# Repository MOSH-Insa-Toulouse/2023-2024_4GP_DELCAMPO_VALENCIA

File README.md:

# **Projet Capteur**

## Introduction 

## Sommaire

***
  - [Livrables](#livrables)
  - [PCB Shield](#pcb-shield)
  - [Code Arduino de Mesure](#code-arduino-de-mesure)
  - [APK pour Android](#apk-pour-android)
  - [Banc de test](#banc-de-test)
  - [Code Arduino de Mesure](#code-arduino-de-mesure)
  - [Datasheet du capteur graphite](#datasheet-du-capteur-graphite)
  - [Problèmes et améliorations](#problèmes-et-améliorations)
  - [Remerciements et contact](#remerciements-et-contacts)

## Livrables

Les livrables pour ce projet sont :
 - [ ] Code Arduino permettant la mesure de R du capteur et pilotage des composants (BT, Potentiomètre, OLED)
 - [ ] PCB du Shield Arduino
 - [ ] APK Android pour le pilotage du système via smartphone
 - [ ] Datasheet du capteur de graphite
 - [ ] Banc de test pour étude du capteur sous différents types de grpahite ( 2B, HB, etc...)

## Matériel

 - 1 carte [Arduino UNO](https://store.arduino.cc/products/arduino-uno-rev3)
 - 1 écran [OLED-01](https://www.gotronic.fr/art-afficheur-oled-0-96-i2c-oled01-31506.htm)
 - 1 AOP [LTC1050](https://www.analog.com/en/products/ltc1050.html)
 - 1 Potentiomètre digital [MCP-41050](https://www.microchip.com/en-us/product/mcp41050)
 - 1 Module Bluetooth [HC-05](https://www.gotronic.fr/art-module-bluetooth-hc05-26097.htm)
 - 1 Encodeur Rotatoire [KY-040](https://www.az-delivery.de/fr/products/drehimpulsgeber-modul)
 - Résistances (X2 100kOhm, X1 1kOhm)
 - Condensateurs (X2 100nF, X1 1uF)
 - Crayons (HB, 2B,...)
 - Modèle papier pour capteur

## PCB Shield

### Symboles et empreintes des composants

### Schématique

### Placement et routage sur PCB

### Modèle 3D

### Soudage du PCB

## Code Arduino de Mesure

## APK pour Android

## Banc de test

## Datasheet

## Problèmes et améliorations

## Remerciements et contacts

**Contact:**
 - Ignacio DEL CAMPO : delcampo@insa-toulouse.fr
 - Izan VALENCIA : ivalenci@insa-toulouse.fr

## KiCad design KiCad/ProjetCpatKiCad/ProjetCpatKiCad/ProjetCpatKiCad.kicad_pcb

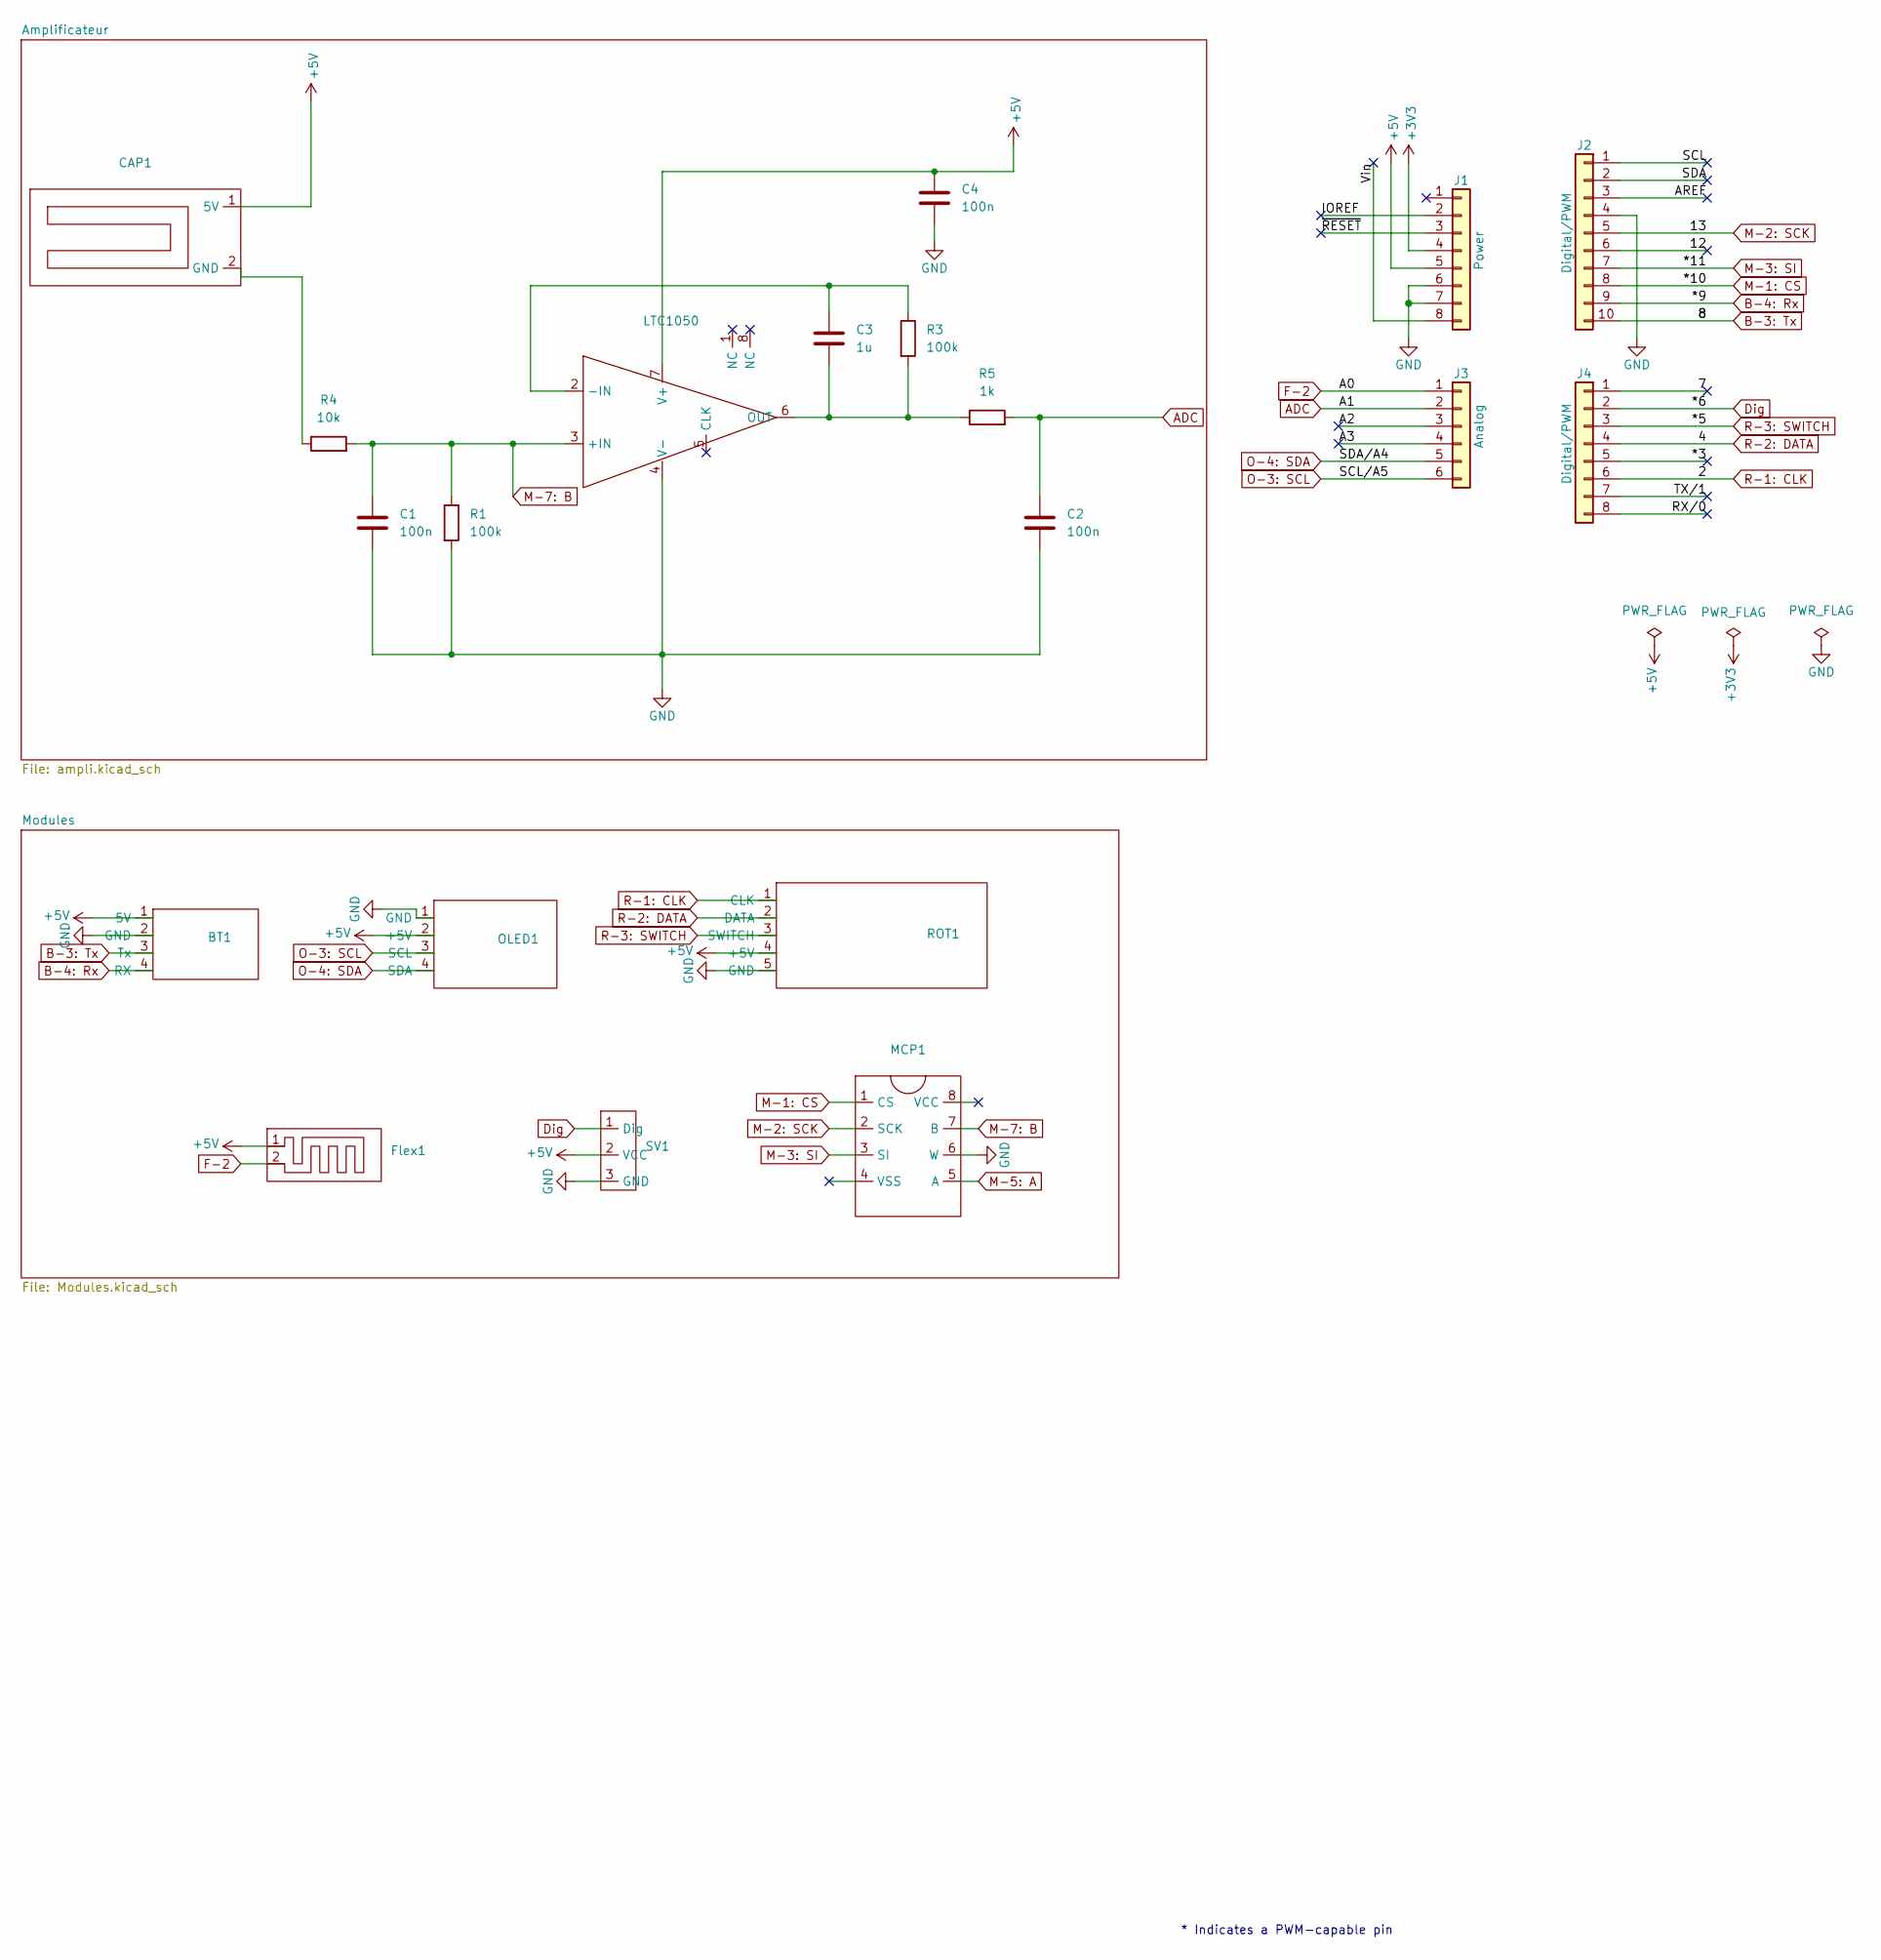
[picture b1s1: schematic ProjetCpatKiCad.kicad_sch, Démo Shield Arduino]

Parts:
BT1: BT-HC05
C1, C2: 100n; C_Axial_L3.8mm_D2.6mm_P7.50mm_Horizontal
C3: 1u; C_Axial_L3.8mm_D2.6mm_P7.50mm_Horizontal
C4: 100n; C_Rect_L4.6mm_W5.5mm_P2.50mm_MKS02_FKP02
CAP1: Capteur Gaz
Flex1: Flexeo
J1: Power; PinSocket_1x08_P2.54mm_Vertical
J2: Digital/PWM; PinSocket_1x10_P2.54mm_Vertical
J3: Analog; PinSocket_1x06_P2.54mm_Vertical
J4: Digital/PWM; PinSocket_1x08_P2.54mm_Vertical
LTC1050: LTC1050
MCP1: DigiPot
OLED1: OLED
R1, R3: 100k; R_Axial_DIN0204_L3.6mm_D1.6mm_P1.90mm_Vertical
R4: 10k; R_Axial_DIN0204_L3.6mm_D1.6mm_P1.90mm_Vertical
R5: 1k; R_Axial_DIN0204_L3.6mm_D1.6mm_P1.90mm_Vertical
ROT1: ROT
SV1: SIP-3

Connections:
+3V3: J1.4
+5V: BT1.1 (5V), C4.1, CAP1.1 (5V), Flex1.1, J1.5, LTC1050.7 (V+), OLED1.2 (+5V), ROT1.4 (+5V), SV1.2 (VCC)
/7: J4.1
/12: J2.6
/*3: J4.5
/A2: J3.3
/A3: J3.4
/AREF: J2.3
/IOREF: J1.2
/RX/0: J4.8
/SCL: J2.1
/SDA: J2.2
/TX/1: J4.7
/Vin: J1.8
/~RESET: J1.3
ADC: C2.1, J3.2, R5.2
B-3: Tx: BT1.3 (Tx), J2.10
B-4: Rx: BT1.4 (RX), J2.9
Dig: J4.2, SV1.1 (Dig)
F-2: Flex1.2, J3.1
GND: BT1.2 (GND), C1.2, C2.2, C4.2, J1.6, J1.7, J2.4, LTC1050.4 (V-), MCP1.6 (W), OLED1.1 (GND), R1.2, ROT1.5 (GND), SV1.3 (GND)
M-1: CS: J2.8, MCP1.1 (CS)
M-2: SCK: J2.5, MCP1.2 (SCK)
M-3: SI: J2.7, MCP1.3 (SI)
M-5: A: MCP1.5 (A)
M-7: B: C1.1, LTC1050.3 (+IN), MCP1.7 (B), R1.1, R4.2
unnamed: CAP1.2 (GND), R4.1
unnamed: C3.1, LTC1050.2 (-IN), R3.1
unnamed: C3.2, LTC1050.6 (OUT), R3.2, R5.1
O-3: SCL: J3.6, OLED1.3 (SCL)
O-4: SDA: J3.5, OLED1.4 (SDA)
R-1: CLK: J4.6, ROT1.1 (CLK)
R-2: DATA: J4.4, ROT1.2 (DATA)
R-3: SWITCH: J4.3, ROT1.3 (SWITCH)

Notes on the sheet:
* Indicates a PWM-capable pin

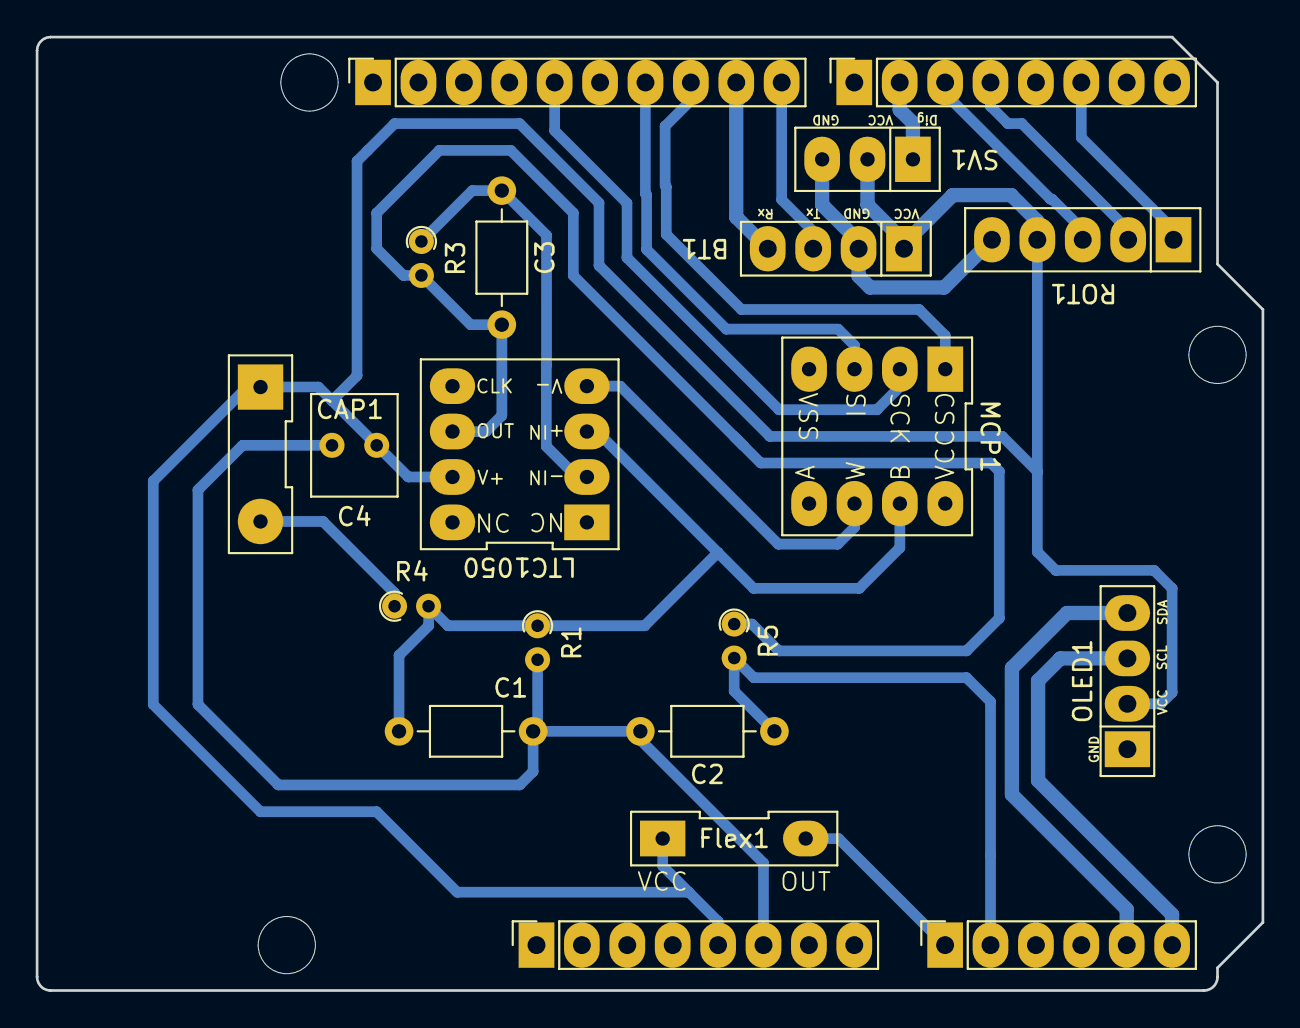
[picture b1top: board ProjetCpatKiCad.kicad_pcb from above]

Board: 2 copper layers, 68.6 x 53.3 mm, 24 parts (0 on the bottom side), 19 nets.

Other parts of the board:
MH1, MH2, MH3, MH4: MountingHole_3.2mm

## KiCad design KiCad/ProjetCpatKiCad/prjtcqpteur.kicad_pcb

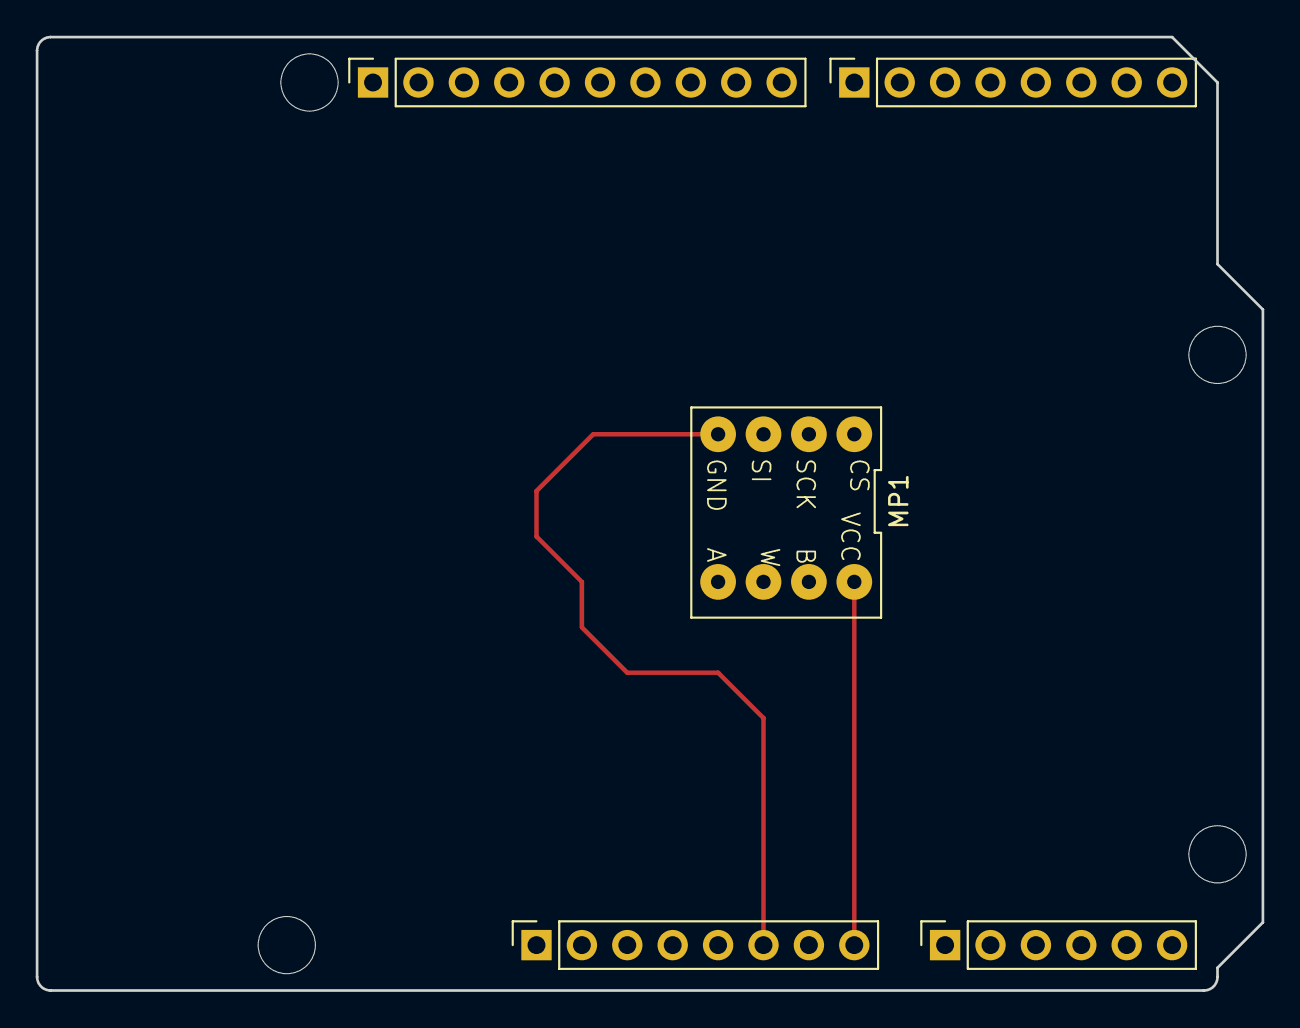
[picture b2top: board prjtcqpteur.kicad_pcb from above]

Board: 2 copper layers, 68.6 x 53.3 mm, 9 parts (0 on the bottom side), 4 nets.

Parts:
J1: Power; PinSocket_1x08_P2.54mm_Vertical
J2: Digital/PWM; PinSocket_1x10_P2.54mm_Vertical
J3: Analog; PinSocket_1x06_P2.54mm_Vertical
J4: Digital/PWM; PinSocket_1x08_P2.54mm_Vertical
MH1, MH2, MH3, MH4: MountingHole_3.2mm
MP1: MCP41050

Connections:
/SCL/A5: J2.1, J3.6
/SDA/A4: J2.2, J3.5
GND: J1.6, J1.7, J2.4, MP1.4 (VSS)
VCC: J1.8, MP1.8 (VCC)

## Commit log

2024-02-16 version initiale du projet
2024-02-16 pa probar
2024-02-16 Quité enters
2024-03-01 Create README2
2024-03-01 holi
2024-03-01 MainProgram Added to folder
2024-03-01 Ajustes de carpetas
2024-03-01 Cambios TD1 Kicad
2024-03-01 TD1.1 Chages to KIDCAD
2024-03-01 ChangementFIchierCodeINO
2024-03-03 AddedLibraries on ProgrammePrincipal
2024-03-03 Added FolderToProgrammePrincipal
2024-03-04 NoMoreProgOnVSCode
2024-03-04 Create LICENSE
2024-03-04 Édition du programme principal
2024-03-04 AjoutPartieOLED
2024-03-08 Add files via upload
    MCP 41050
2024-03-08 KICAD modifs
2024-03-08 Add files via upload
    solo con comentarios extra
2024-03-08 More kicad modifs
2024-03-08 Duri
2024-03-08 biblioteca chulo mcp 41050
2024-03-08 Modifs
2024-03-08 more
2024-03-08 kicad
2024-03-08 KICAD final 08/03
2024-03-10 Cambios KICAD
2024-03-10 KICAD connections
2024-03-10 Create FicheTemps.md
    Fiche pour mesurer le temps passé sur le projet capteur
2024-03-11 Añadidos librerias KICAD
2024-03-11 Footprints and schematics
2024-03-11 Programme menu
2024-03-11 Librairie footprint ProjetCpatKiCad
2024-03-12 un poquito de pcb
2024-03-12 Codage Arduino
2024-03-12 tiqui
2024-03-14 Kicad routage
2024-03-14 Changements Arduino
2024-03-14 VIA GND
2024-03-14 Final Changes
2024-03-14 Kicad modelos 3d
2024-03-22 Modifs pour application
2024-03-22 Kicad con servo
2024-03-23 Commentaires sur code
2024-03-25 kikadfinal
    Dale visto bueno
2024-03-25 Cambios para APP
2024-03-25 FicheTemps Update
2024-03-26 Chagments Code BT
2024-03-26 otro
2024-03-26 BT FUNCIONAAA
2024-03-27 Changements Arduino+ APK sur GIT
2024-03-27 Actualizar README.md
2024-03-28 Changes PINS R et C
